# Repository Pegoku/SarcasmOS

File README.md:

# SarcasmOS

SarcasmOS is a personality-first voice assistant.
The core idea is simple: take a smart assistant like Alexa or Google Home, then give it a face, a voice, and most importantly, a personality. Instead of answering like a neutral corporate box, SarcasmOS replies in Spanish with dry humor, sarcasm, and animated expressions inspired by [Bender](https://futurama.fandom.com/wiki/Bender).

This project focusses on the software and AI side of the assistant, but it also includes various hardware elements, like multiple PCBs, sensors, motors, and quite a bit of 3D printing.
The goal is to have a memorable, sarcastic, and show-like assistant that can be used both for fun and real tasks like controlling smart home devices, playing music reviewing your agenda, or answering questions.

### Demo Video

<details>
  <summary>Do not click here</summary>

</details>

## Why did we Build This?

Futurama is a classic tv show we love (and you should too). Bender is the most memorable character, and his sarcastic personality is a perfect fit for a voice assistant.
We wanted to build a voice assistant that is not just a plain, neutral box, but one that has a personality and you won't just use it to get things done, but also to have fun and be entertained

## Images

<details>
  <summary>CAD - click to expand</summary>

</details>

### Brain PCB

<details>
  <summary>Brain PCB schematic - click to expand</summary>

</details>

<details>
  <summary>Brain PCB layout - click to expand</summary>

</details>

### Eye PCB

<details>
  <summary>Eye PCB schematic - click to expand</summary>

</details>

<details>
  <summary>Eye PCB layout - click to expand</summary>

</details>

### Mouth PCB

<details>
  <summary>Mouth PCB schematic - click to expand</summary>

</details>

<details>
  <summary>Mouth PCB layout - click to expand</summary>

</details>

## Language Scope

SarcasmOS is designed to work in Spanish first.

The language model prompt, personality, expected user input, and generated responses are all tuned for Spanish. Other languages may work accidentally depending on the upstream model, but they are outside the intended behavior of this project.

## Features

- Listens to speech input.
- Transcribes speech to text.
- Generates Spanish answers with a sarcastic character voice.
- Converts the answer back to speech.
- Syncs audio playback with an animated face.
- Stores memory of past interactions.
- Has a web interface for chat, audio, history and configuration.
- Has integrated speaker and microphone.
- Custom animations for the eyes and mouth.
- _8k mouth display_ (128x64 pixels = 8192 pixels).

## BOM

> It is recommended to use the online [google spreadsheet](https://docs.google.com/spreadsheets/d/1oUawWcxpkl1FgnUkY16h-4gWlRbnDHgNzrJ1ZsR5Gkk/edit?usp=sharing) for the most up to date BOM with links and prices.

<details>
  <summary>Click to expand the BOM table</summary>

| Item                | Desc                   | Qtty needed | Qtty / Pack | Pack Qtty | Price / pack | Source                                                                                                                                                                                                                                                                                                                                                                                                                                                                                                                                                                                                                                                                                                                                                                                                                                                                                                                                                                                            | Extra                                                                                                                | Category           | Already owned | In Cart | Purchased | Item Total | Final Total | Final Total ($) |
| ------------------- | ---------------------- | ----------- | ----------- | --------- | ------------ | ------------------------------------------------------------------------------------------------------------------------------------------------------------------------------------------------------------------------------------------------------------------------------------------------------------------------------------------------------------------------------------------------------------------------------------------------------------------------------------------------------------------------------------------------------------------------------------------------------------------------------------------------------------------------------------------------------------------------------------------------------------------------------------------------------------------------------------------------------------------------------------------------------------------------------------------------------------------------------------------------- | -------------------------------------------------------------------------------------------------------------------- | ------------------ | ------------- | ------- | --------- | ---------- | ----------- | --------------- |
| Round Display       | Eyes                   | 2           | 2           | 1         | 6.55€        | https://es.aliexpress.com/item/1005006928550245.html?spm=a2g0o.detail.0.0.3380vPbLvPbLqx&mp=1&pdp_npi=6%40dis%21EUR%21EUR+6.99%21EUR+6.99%21%21EUR+6.85%21%21%21%400b88a95617788756053276236e0e02%2112000045970082989%21ct%21NL%213560368449%21%211%210%21&gatewayAdapt=nld2esp                                                                                                                                                                                                                                                                                                                                                                                                                                                                                                                                                                                                                                                                                                                   |                                                                                                                      | Eyes               | FALSE         | TRUE    | FALSE     | 6.55€      | 269.90€     | $309.64         |
| Display Lens        | Make Eyes Bigger       | 2           | 1           | 2         | 19.69€       | https://es.aliexpress.com/item/1005008724449296.html?spm=a2g0o.detail.0.0.6a0760d1eKUq5E&mp=1&pdp_npi=6%40dis%21EUR%21EUR%2020.73%21EUR%2019.69%21%21EUR%2019.69%21%21%21%4021038a8017819666708386757e11aa%2112000046404933342%21ct%21ES%213560368449%21%211%210%21&gatewayAdapt=glo2esp                                                                                                                                                                                                                                                                                                                                                                                                                                                                                                                                                                                                                                                                                                          |                                                                                                                      | Eyes               | FALSE         | FALSE   | FALSE     | 39.38€     |             |                 |
| Flexible LED Matrix | Mouth                  | 1           | 2           | 1         | 39.56€       | https://es.aliexpress.com/item/1005006068032826.html?spm=a2g0o.productlist.main.21.139eA4CxA4Cx4e&algo_pvid=5b077f7f-89aa-40ed-b4d1-d402daa6e2e7&pdp_ext_f=%7B%22order%22%3A%225%22%2C%22eval%22%3A%221%22%2C%22fromPage%22%3A%22search%22%7D&utparam-url=scene%3Asearch%7Cquery_from%3A%7Cx_object_id%3A1005006068032826%7C_p_origin_prod%3A&gatewayAdapt=nld2esp                                                                                                                                                                                                                                                                                                                                                                                                                                                                                                                                                                                                                                |                                                                                                                      | Mouth              | FALSE         | FALSE   | FALSE     | 39.56€     |             |                 |
| Microphone module   | Fallback PCB           | 1           | 1           | 1         | 6.30€        | https://es.aliexpress.com/item/1005009698505728.html?spm=a2g0o.cart.0.0.6c4d38daLbAysv&mp=1&pdp_npi=6%40dis%21EUR%21EUR+14.93%21EUR+6.24%21%21EUR+6.24%21%21%21%400b8848e317816378509391522e0e93%2112000049889234983%21ct%21ES%213560368449%21%211%210%21&gatewayAdapt=glo2esp                                                                                                                                                                                                                                                                                                                                                                                                                                                                                                                                                                                                                                                                                                                    |                                                                                                                      | Brain              | FALSE         | FALSE   | FALSE     | 6.30€      |             |                 |
| Ethernet module     | Fallback PCB           | 1           | 1           | 1         | 4.35€        | https://es.aliexpress.com/item/1005009204216561.html?spm=a2g0o.detail.pcDetailBottomMoreOtherSeller.3.6e6eUfXQUfXQ5C&gps-id=pcDetailBottomMoreOtherSeller&scm=1007.40050.354490.0&scm_id=1007.40050.354490.0&scm-url=1007.40050.354490.0&pvid=3570e6de-c66e-4314-adfb-729cb482450e&_t=gps-id%3ApcDetailBottomMoreOtherSeller%2Cscm-url%3A1007.40050.354490.0%2Cpvid%3A3570e6de-c66e-4314-adfb-729cb482450e%2Ctpp_buckets%3A668%232846%238114%231999&pdp_ext_f=%7B%22order%22%3A%22295%22%2C%22spu_best_type%22%3A%22price%22%2C%22eval%22%3A%221%22%2C%22sceneId%22%3A%2230050%22%2C%22fromPage%22%3A%22recommend%22%7D&pdp_npi=6%40dis%21EUR%214.69%214.69%21%21%215.33%215.33%21%402103973d17801598614361290e0f38%2112000048290449884%21rec%21NL%213560368449%21X%211%210%21n_tag%3A-29919%3Bd%3Adc2a0b43%3Bm03_new_user%3A-29895&utparam-url=scene%3ApcDetailBottomMoreOtherSeller%7Cquery_from%3A%7Cx_object_id%3A1005009204216561%7C_p_origin_prod%3A&gatewayAdapt=nld2esp#nav-specification |                                                                                                                      | Brain              | FALSE         | FALSE   | FALSE     | 4.35€      |             |                 |
| 18650 cells         |                        | 14          | 1           | 14        | 0.00€        | Already owned                                                                                                                                                                                                                                                                                                                                                                                                                                                                                                                                                                                                                                                                                                                                                                                                                                                                                                                                                                                     |                                                                                                                      | Brain              | TRUE          | FALSE   | FALSE     | 0          |             |                 |
| cable               |                        | 1           | 1           | 1         | 0.00€        | Already owned                                                                                                                                                                                                                                                                                                                                                                                                                                                                                                                                                                                                                                                                                                                                                                                                                                                                                                                                                                                     |                                                                                                                      | Brain              | FALSE         | FALSE   | FALSE     | 0.00€      |             |                 |
| mmWave sensor       |                        | 1           | 1           | 1         | 4.79€        | https://es.aliexpress.com/item/1005006121923099.html?spm=a2g0o.detail.0.0.791e7F4F7F4Fcg&mp=1&pdp_npi=6%40dis%21EUR%21EUR%204.92%21EUR%204.89%21%21EUR%204.89%21%21%21%402103842a17788752854925679e1108%2112000035851121206%21ct%21NL%213560368449%21%211%210%21&gatewayAdapt=nld2esp                                                                                                                                                                                                                                                                                                                                                                                                                                                                                                                                                                                                                                                                                                             |                                                                                                                      | Brain              | TRUE          | FALSE   | FALSE     | 0          |             |                 |
| Stepper Motor       | Nema17 17HS4023 42BGYH | 1           | 1           | 1         | 5.19€        | https://es.aliexpress.com/item/1005003874936862.html?spm=a2g0o.productlist.main.2.45ac6b6d4Ty51H&algo_pvid=24c1815d-4fc5-48d3-8530-a3506b98d7ee&pdp_ext_f=%7B%22order%22%3A%227968%22%2C%22spu_best_type%22%3A%22price%22%2C%22eval%22%3A%221%22%2C%22fromPage%22%3A%22search%22%7D&utparam-url=scene%3Asearch%7Cquery_from%3A%7Cx_object_id%3A1005003874936862%7C_p_origin_prod%3A                                                                                                                                                                                                                                                                                                                                                                                                                                                                                                                                                                                                               |                                                                                                                      | Brain              | FALSE         | FALSE   | FALSE     | 5.19€      |             |                 |
| Antenna             | For esp32              | 1           | 1           | 1         | 1.84€        | https://es.aliexpress.com/item/1005007468291772.html                                                                                                                                                                                                                                                                                                                                                                                                                                                                                                                                                                                                                                                                                                                                                                                                                                                                                                                                              |                                                                                                                      | Brain              | FALSE         | FALSE   | FALSE     | 1.84€      |             |                 |
| Speakers            | Speakers               | 1           | 2           | 1         | 5.47€        | https://es.aliexpress.com/item/1005008326457654.html?spm=a2g0o.productlist.main.3.25f622deCmRsMj&algo_pvid=bae0d8d2-8cd9-44f2-b28e-96956b2241be&algo_exp_id=bae0d8d2-8cd9-44f2-b28e-96956b2241be-2&pdp_ext_f=%7B%22order%22%3A%22415%22%2C%22eval%22%3A%221%22%2C%22fromPage%22%3A%22search%22%7D&pdp_npi=6%40dis%21EUR%215.66%215.49%21%21%2143.88%2142.56%21%402103835c17752449159045745eacb9%2112000044613535197%21sea%21NL%213560368449%21X%211%210%21n_tag%3A-29919%3Bd%3Adc2a0b43%3Bm03_new_user%3A-29895&curPageLogUid=PrDyQ5hqmN9h&utparam-url=scene%3Asearch%7Cquery_from%3A%7Cx_object_id%3A1005008326457654%7C_p_origin_prod%3A&gatewayAdapt=nld2esp                                                                                                                                                                                                                                                                                                                                   |                                                                                                                      | Brain              | FALSE         | FALSE   | FALSE     | 5.47€      |             |                 |
| LCSC components     | Components             | 1           | 1           | 1         | 93.44€       | https://www.lcsc.com                                                                                                                                                                                                                                                                                                                                                                                                                                                                                                                                                                                                                                                                                                                                                                                                                                                                                                                                                                              | https://docs.google.com/spreadsheets/d/1oUawWcxpkl1FgnUkY16h-4gWlRbnDHgNzrJ1ZsR5Gkk/edit?gid=283679690#gid=283679690 | Brain, Mouth, Eyes | FALSE         | FALSE   | FALSE     | 93.44€     |             |                 |
| LCSC Shipping       | Components             | 1           | 1           | 1         | 14.68€       | https://www.lcsc.com                                                                                                                                                                                                                                                                                                                                                                                                                                                                                                                                                                                                                                                                                                                                                                                                                                                                                                                                                                              |                                                                                                                      | Brain, Mouth, Eyes | FALSE         | FALSE   | FALSE     | 14.68€     |             |                 |
| JLCPCB PCBs         | PCBs                   | 1           | 1           | 1         | 22.17€       | http://jlcpcb.com                                                                                                                                                                                                                                                                                                                                                                                                                                                                                                                                                                                                                                                                                                                                                                                                                                                                                                                                                                                 |                                                                                                                      | Brain, Mouth, Eyes | FALSE         | FALSE   | FALSE     | 22.17€     |             |                 |
| JLCPCB Shipping     | PCBs                   | 1           | 1           | 1         | 30.97€       | http://jlcpcb.com                                                                                                                                                                                                                                                                                                                                                                                                                                                                                                                                                                                                                                                                                                                                                                                                                                                                                                                                                                                 | THIS IS THE CHEAPEST OPTION                                                                                          | Brain, Mouth, Eyes | FALSE         | FALSE   | FALSE     | 30.97€     |             |                 |

</details>

## Current State

SarcasmOS is complete, including its Brain, Eye, and Mouth firmware. The finished hardware can listen for its wake phrase, understand a spoken request, use tools, answer in a Spanish Bender-style voice, and coordinate the animated face while it works and speaks.

| Component                                 | Capabilities                                                                                                                                                                                                                                                                                                                                                        |
| ----------------------------------------- | ------------------------------------------------------------------------------------------------------------------------------------------------------------------------------------------------------------------------------------------------------------------------------------------------------------------------------------------------------------------- |
| [Brain firmware](Code/Brain)              | Runs the complete voice-assistant workflow on the ESP32-S3: microphone capture, wake-phrase detection, STT, multi-round LLM calls, TTS, speaker playback, conversation memory, a USB console, and a local HTTP API. Its native tools provide weather, local time, Google Calendar search, and live robot status. It also coordinates synchronized face transitions. |
| [Eye firmware](Code/Eye)                  | Drives the two 240x240 GC9A01A displays from RP2040 boards, with 31 animated expression and weather states, independent left/right artwork, brightness control, and synchronized transitions over I2C.                                                                                                                                                              |
| [Mouth firmware](Code/Mouth-NeonPCB)      | Drives the 64x32 HUB75 RGB matrix from an ESP32-S3, with the matching 31 states, blended transitions, speaking intensity, live weather temperatures, brightness control, and acknowledged ESP-NOW communication.                                                                                                                                                    |
| [Web app](Code/AI/Workflow/SarcasmOS-web) | Provides an optional browser interface with chat, voice, history, configuration, and a full-face view. A hosted demo is available at [sarcasmos.pegoku.com](https://sarcasmos.pegoku.com/).                                                                                                                                                                         |
| Hardware                                  | Includes the finished 3D-printed enclosure, Brain/Eye/Mouth PCBs, microphone, speakers, sensors, motors, and display hardware.                                                                                                                                                                                                                                      |

The Brain is the runtime controller: it talks to the two Eyes over I2C and to
the Mouth over acknowledged ESP-NOW. STT, LLM, and TTS remain cloud services,
but the physical assistant does not require the Python web backend to run.

## Build and Run the Firmware

Bring the boards up in this order so the Brain can be configured with the
Mouth's MAC address and matching 2.4 GHz Wi-Fi/ESP-NOW channel.

### 1. Mouth

Install [PlatformIO](https://platformio.org/), connect the Mouth ESP32-S3, and
run:

```bash
cd Code/Mouth-NeonPCB
pio run -e custom_esp32s3_mini_n8 --target upload
pio device monitor -e custom_esp32s3_mini_n8
```

At boot, note the station MAC address and ESP-NOW channel printed in the serial
monitor. The Mouth uses channel 1 by default; its onboard button can select
channels 1 through 13. It must match the Brain's Wi-Fi channel. See the
[Mouth firmware guide](Code/Mouth-NeonPCB/README.md) for local animation tests,
panel wiring, channel controls, and display emulation.

### 2. Eyes

Install the [Raspberry Pi Pico SDK](https://github.com/raspberrypi/pico-sdk),
connect each RP2040 Eye through SWD, and flash the regular I2C firmware:

```bash
cd Code/Eye
./flash.sh --left --regular --build --upload --swd-monitor
./flash.sh --right --regular --build --upload --swd-monitor
```

The left and right Eyes use I2C addresses `0x30` and `0x31`, respectively.
The helper also provides self-test and standalone animation-demo firmware. See
the [Eye firmware guide](Code/Eye/README.md) for OpenOCD setup, manual builds,
UART monitoring, alternate animation packs, and the desktop editor.

### 3. Brain

Install [ESP-IDF](https://docs.espressif.com/projects/esp-idf/en/stable/esp32s3/get-started/index.html),
connect the Brain ESP32-S3, and run:

```bash
cd Code/Brain
idf.py set-target esp32s3
idf.py menuconfig
idf.py build
idf.py flash monitor
```

Under **SarcasmOS Brain** in `menuconfig`, set the Wi-Fi credentials, provider
tokens, TTS voice ID, timezone, and the Mouth station MAC recorded above. You
can also configure the wake phrase, audio sensitivity, Eye transition timing,
and ESP-NOW channel. After flashing, the USB console can test every subsystem,
send typed or spoken requests, and update persistent configuration stored in
NVS. See the [Brain firmware guide](Code/Brain/README.md) for all settings,
console commands, API endpoints, native tools, and the independent PCB
self-test firmware.

## Web Demo

For the already setup web demo, visit [https://sarcasmos-7f3c9a2e.easyrumbo.com/](https://sarcasmos-7f3c9a2e.easyrumbo.com/).

For the best experience and no ratelimiting, run the local web app.

From `Code/AI/Workflow/SarcasmOS-web`:

```bat
start-all.bat
```

On macOS/Linux:

```bash
./start-all.sh
```

This starts:

- Proxy (combines all services into 1 port for easy access): `http://localhost:9000`
- Frontend: `http://localhost:5173`
- Backend: `http://localhost:8001`

You can also start them separately:

```bash
python -m http.server 5173
python -m uvicorn backend.app:app --host 0.0.0.0 --port 8001
```

## Configuration

The backend reads environment variables from `.env` files, especially:

- `Code/AI/Workflow/SarcasmOS-web/backend/.env`
- `Code/AI/Workflow/.env`

**Important variables**:

- `HACK_CLUB_AI_KEY`, or separate provider keys.
- `OPENROUTER_API_TOKEN` for the language model.
- `REPLICATE_API_TOKEN` for STT/TTS if using Replicate.
- `MINIMAX_VOICE_ID` for the TTS voice.
- `FFMPEG_PATH` if `ffmpeg` is not available on PATH.

More technical detail:

- `Code/AI/Workflow/SarcasmOS-web/README.md`
- `Code/AI/Workflow/SarcasmOS-web/PROJECT_OVERVIEW.md`

## Architecture

```text
Microphone / wake phrase / text request
                  |
                  v
          ESP32-S3 Brain
           |      |      \
           |      |       +--> Cloud STT, LLM/tools, and TTS
           |      |
           |      +----------> Mouth over ESP-NOW
           |
           +-----------------> Left + right Eyes over I2C
                  |
                  v
       Speaker audio + synchronized animated face
```

## Things that happened when carrying out the project

When it came to making our project a reality we had several problems, because of customs we had to pay almost $200 more than what we had budgeted. We ended up paying more than $600 for the project 😭

When we ordered the electronic components, 4 were missing, for some reason. We told the company and they sent us the missing components (they were less than $1). When they arrived, which they did way after we finshed the project, and they wanted us to pay customs more than $16 for $0.80 of chips...

The flexible display we wanted to use also got lost in the mail, and we had to pay $60 for one, but it didn't arrive either. We ended up using a different display and driver, which we already had from a previos Hackclub YSWS (Neon).

## Credits

Built as a physical AI assistant project for Hack Club / Fallout.
SarcasmOS is not trying to be polite. It is trying to be memorable.

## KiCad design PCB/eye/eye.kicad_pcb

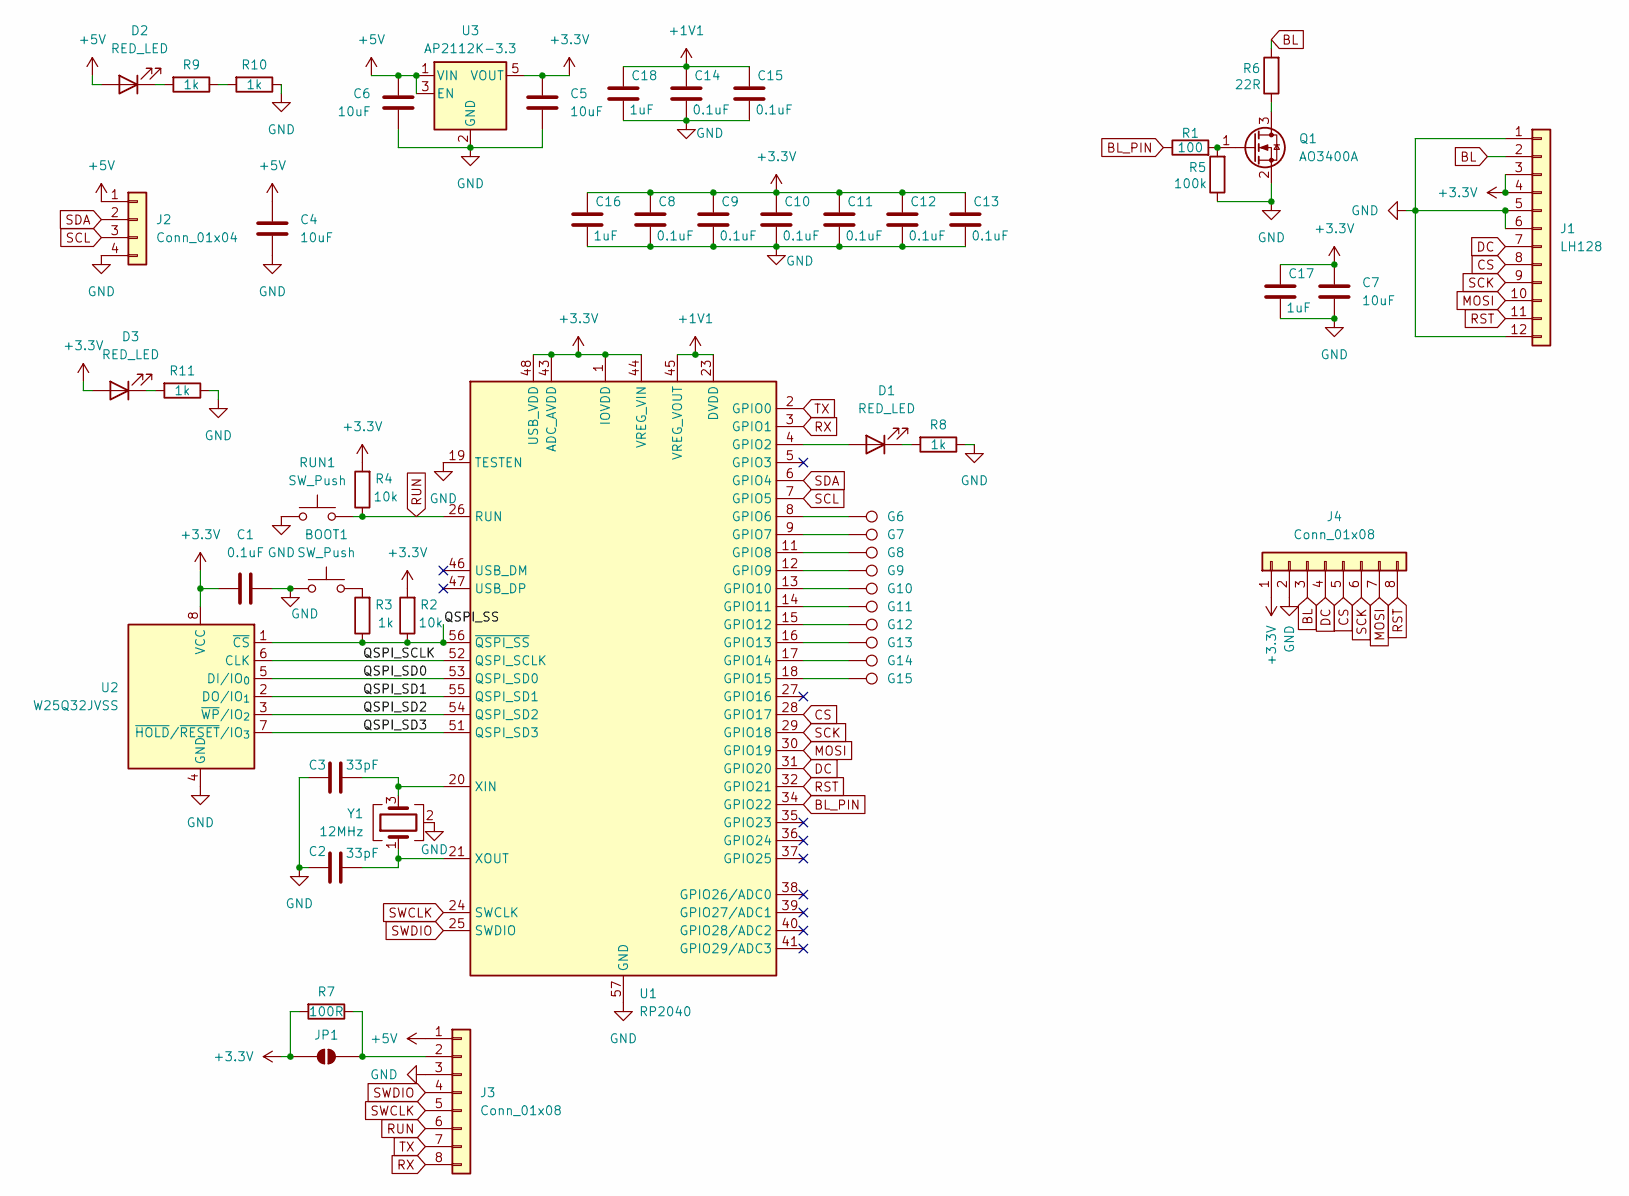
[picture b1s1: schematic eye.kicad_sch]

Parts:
BOOT1: SW_Push; SW_SPST_TS-1088-xR025; LCSC Part C720477
C1, C8, C9, C10, C11, C12, C13, C14, C15: 0.1uF; C_0603_1608Metric
C2, C3: 33pF; C_0603_1608Metric; LCSC Part C1663
C4, C5, C6, C7: 10uF; C_0805_2012Metric
C16, C17, C18: 1uF; C_0603_1608Metric
D1, D2, D3: RED_LED; LED_0603_1608Metric; LCSC Part C19171390
G6, G7, G8, G9, G10, G11, G12, G13, G14, G15: TestPoint; TestPoint_Pad_D1.0mm
J1: LH128; LH128R
J2: Conn_01x04; JST_XH_B4B-XH-A_1x04_P2.50mm_Vertical; LCSC Part C144395
J3, J4: Conn_01x08; PinHeader_2x04_P2.54mm_Vertical; LCSC Part C5383105
JP1: SolderJumper_2_Open; SolderJumper-2_P1.3mm_Open_TrianglePad1.0x1.5mm
Q1: AO3400A; SOT-23
R1: 100; R_0603_1608Metric
R2, R4: 10k; R_0603_1608Metric
R3, R8, R9, R10, R11: 1k; R_0603_1608Metric
R5: 100k; R_0603_1608Metric
R6: 22R; R_0603_1608Metric
R7: 100R; R_0603_1608Metric
RUN1: SW_Push; SW_SPST_TS-1088-xR025; LCSC Part C720477
U1: RP2040; QFN-56-1EP_7x7mm_P0.4mm_EP3.2x3.2mm; LCSC Part C2040
U2: W25Q32JVSS; SOIC-8_5.3x5.3mm_P1.27mm
U3: AP2112K-3.3; SOT-23-5
Y1: 12MHz; Crystal_SMD_3225-4Pin_3.2x2.5mm; LCSC Part C9002

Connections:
+1V1: C14.2, C15.2, C18.2, U1.23 (DVDD), U1.45 (VREG_VOUT), U1.50 (DVDD)
+3.3V: C1.1, C5.2, C7.2, C8.2, C9.2, C10.2, C11.2, C12.2, C13.2, C16.2, C17.2, D3.2 (A), J1.3, J1.4, J4.1, JP1.1 (A), R2.2, R4.2, R7.2, U1.1 (IOVDD), U1.10 (IOVDD), U1.22 (IOVDD), U1.33 (IOVDD), U1.42 (IOVDD), U1.43 (ADC_AVDD), U1.44 (VREG_VIN), U1.48 (USB_VDD), U1.49 (IOVDD), U2.8 (VCC), U3.5 (VOUT)
+5V: C4.2, C6.2, D2.2 (A), J2.1, J3.1, U3.1 (VIN), U3.3 (EN)
/QSPI_SCLK: U1.52 (QSPI_SCLK), U2.6 (CLK)
/QSPI_SD0: U1.53 (QSPI_SD0), U2.5 (DI/IO_{0})
/QSPI_SD1: U1.55 (QSPI_SD1), U2.2 (DO/IO_{1})
/QSPI_SD2: U1.54 (QSPI_SD2), U2.3 (~WP/IO_{2})
/QSPI_SD3: U1.51 (QSPI_SD3), U2.7 (~HOLD/~RESET/IO_{3})
/QSPI_SS: R2.1, R3.1, U1.56 (~QSPI_SS), U2.1 (~CS)
BL: J1.2, J4.3, R6.2
BL_PIN: R1.1, U1.34 (GPIO22)
CS: J1.8, J4.5, U1.28 (GPIO17)
DC: J1.7, J4.4, U1.31 (GPIO20)
GND: BOOT1.1, C1.2, C2.1, C3.1, C4.1, C5.1, C6.1, C7.1, C8.1, C9.1, C10.1, C11.1, C12.1, C13.1, C14.1, C15.1, C16.1, C17.1, C18.1, J1.1, J1.5, J1.6, J1.12, J2.4, J3.3, J4.2, Q1.2 (S), R5.1, R8.1, R10.1, R11.1, RUN1.1, U1.19 (TESTEN), U1.57 (GND), U2.4 (GND), U3.2 (GND), Y1.2 (G), Y1.4 (G)
MOSI: J1.10, J4.7, U1.30 (GPIO19)
unnamed: BOOT1.2, R3.2
unnamed: D1.2 (A), U1.4 (GPIO2)
unnamed: D1.1 (K), R8.2
unnamed: D2.1 (K), R9.2
unnamed: D3.1 (K), R11.2
unnamed: J3.2, JP1.2 (B), R7.1
unnamed: Q1.3 (D), R6.1
unnamed: Q1.1 (G), R1.2, R5.2
unnamed: R9.1, R10.2
unnamed: G6.1 (1_1), U1.8 (GPIO6)
unnamed: G7.1 (1_1), U1.9 (GPIO7)
unnamed: G8.1 (1_1), U1.11 (GPIO8)
unnamed: G9.1 (1_1), U1.12 (GPIO9)
unnamed: G10.1 (1_1), U1.13 (GPIO10)
unnamed: G11.1 (1_1), U1.14 (GPIO11)
unnamed: G12.1 (1_1), U1.15 (GPIO12)
unnamed: G13.1 (1_1), U1.16 (GPIO13)
unnamed: G14.1 (1_1), U1.17 (GPIO14)
unnamed: G15.1 (1_1), U1.18 (GPIO15)
unnamed: C3.2, U1.20 (XIN), Y1.3
unnamed: C2.2, U1.21 (XOUT), Y1.1
RST: J1.11, J4.8, U1.32 (GPIO21)
RUN: J3.6, R4.1, RUN1.2, U1.26 (RUN)
RX: J3.8, U1.3 (GPIO1)
SCK: J1.9, J4.6, U1.29 (GPIO18)
SCL: J2.3, U1.7 (GPIO5)
SDA: J2.2, U1.6 (GPIO4)
SWCLK: J3.5, U1.24 (SWCLK)
SWDIO: J3.4, U1.25 (SWDIO)
TX: J3.7, U1.2 (GPIO0)

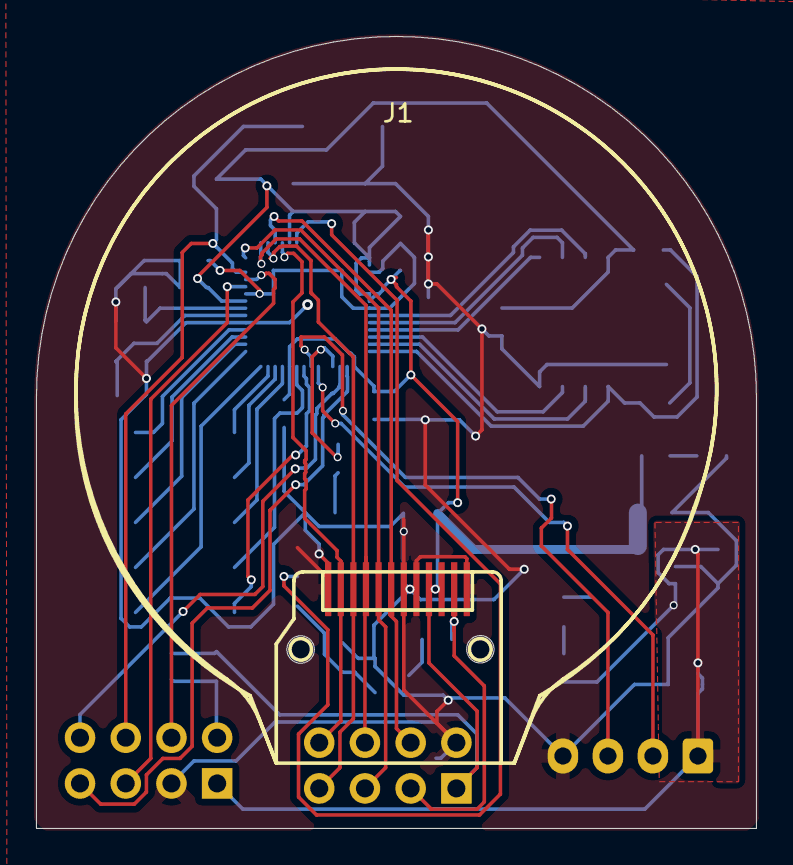
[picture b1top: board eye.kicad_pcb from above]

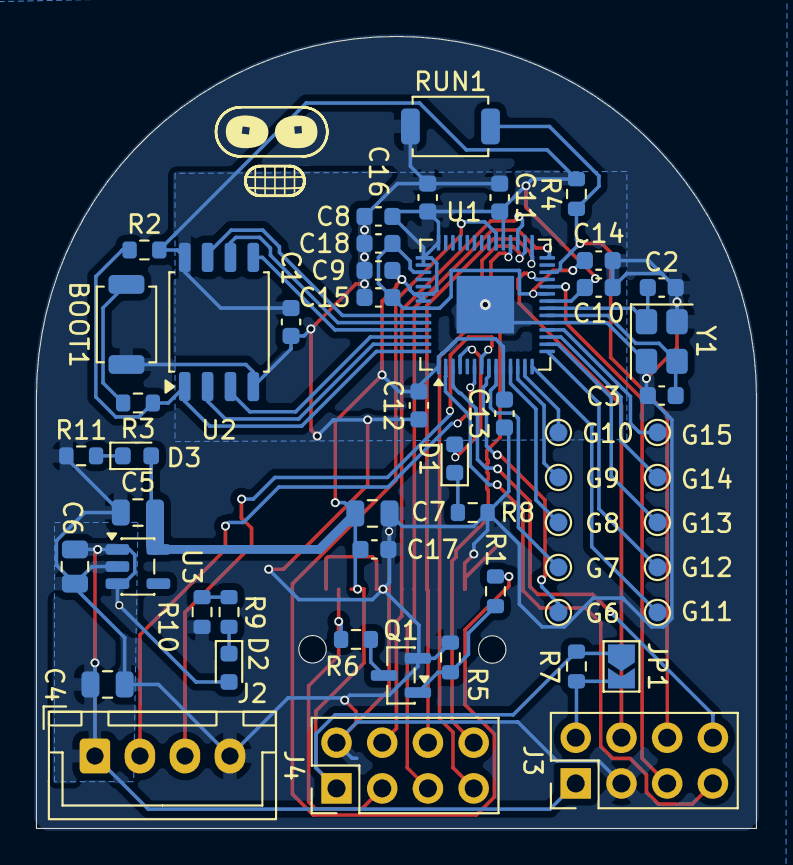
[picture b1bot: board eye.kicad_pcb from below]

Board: 2 copper layers, 40.0 x 44.0 mm, 54 parts (53 on the bottom side), 45 nets.

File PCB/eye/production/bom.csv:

Designator,Footprint,Quantity,Value,LCSC Part #
"BOOT1, RUN1",SW_SPST_TS-1088-xR025,2,SW_Push,C720477
"C1, C10, C11, C12, C13, C14, C15, C8, C9",0603,9,0.1uF,C696916
"C16, C17, C18",0603,3,1uF,C106858
"C2, C3",0603,2,33pF,C1663
"C4, C5, C6, C7",0805,4,10uF,C5448891
"D1, D2, D3",0603,3,RED_LED,C19171390
J1,LH128R,1,LH128,
J2,JST_XH_B4B-XH-A_1x04_P2.50mm_Vertical,1,Conn_01x04,C144395
J3,PinHeader_2x04_P2.54mm_Vertical,1,Conn_01x08,C5383105
J4,PinHeader_2x04_P2.54mm_Vertical,1,Conn_01x08,C5383105
Q1,SOT-23,1,AO3400A,C20917
"R1, R7",0603,2,100R,C5123610
"R10, R11, R3, R8, R9",0603,5,1k,C112433
"R2, R4",0603,2,10k,C2930027
R5,0603,1,100k,C2906980
R6,0603,1,22R,C103434
U1,QFN-56-1EP_7x7mm_P0.4mm_EP3.2x3.2mm,1,RP2040,C2040
U2,SOIC-8_5.3x5.3mm_P1.27mm,1,W25Q128JVSIQ,C97521
U3,SOT-23-5,1,AP2112K-3.3,C51118
Y1,Crystal_SMD_3225-4Pin_3.2x2.5mm,1,12MHz,C9002
